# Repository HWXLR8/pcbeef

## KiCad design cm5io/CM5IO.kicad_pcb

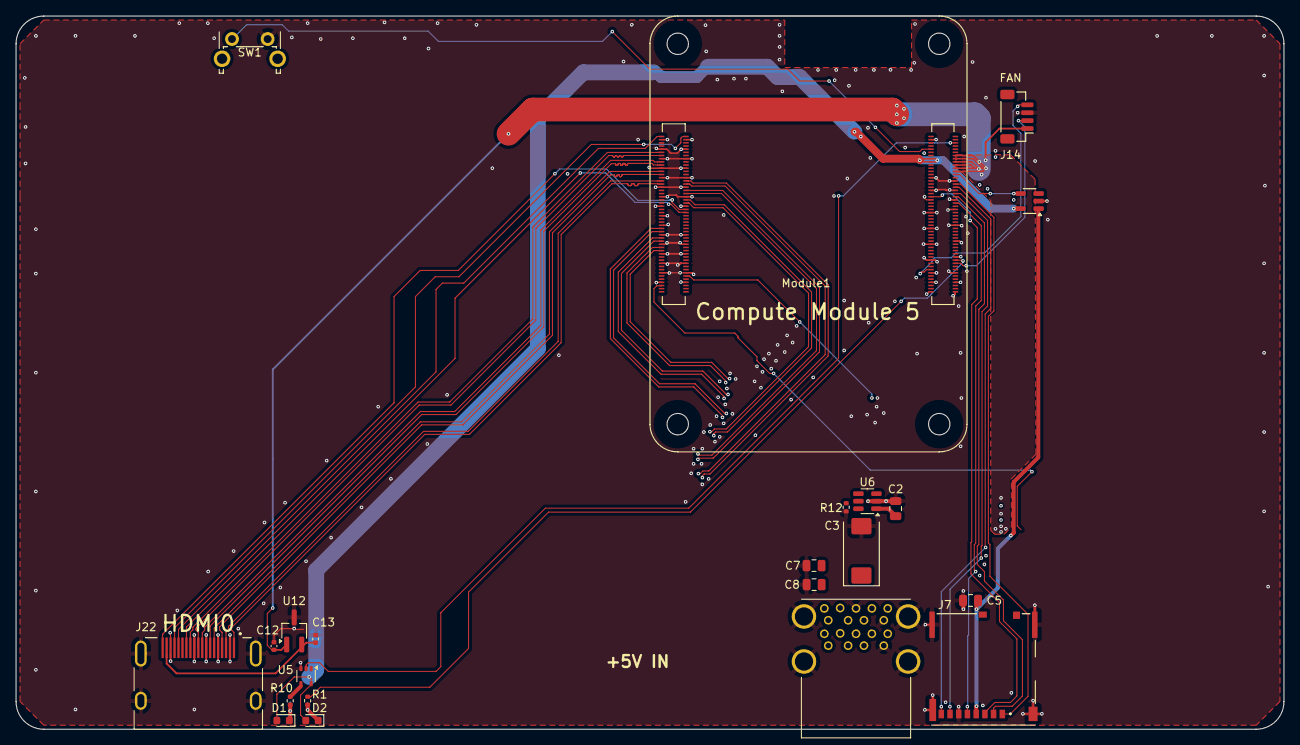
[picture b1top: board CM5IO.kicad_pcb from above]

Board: 4 copper layers, 160.0 x 90.0 mm, 22 parts (0 on the bottom side), 48 nets.

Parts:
C2, C5, C7, C8: 10u; C_0805_2012Metric
C3: 100uF; CP_EIA-7343-31_Kemet-D
C12, C13: 100n; C_0402_1005Metric
D1: LED Red; LED_0603_1608Metric
D2: LED Green; LED_0603_1608Metric
J7: Micro_SD_Card_Det; SDCARD_MOLEX_503398-1892
J12: USB3_A; MTCONN_UBAF30-D2011
J14: JST_SHBM04B-SRSS-TB; JST_SH_BM04B-SRSS-TB_1x04-1MP_P1.00mm_Vertical
J22: 690-019-298-412; EDAC 690-019-298-412
Module1: ComputeModule5-CM5; Raspberry-Pi-5-Compute-Module
R1, R10: 1k; R_0402_1005Metric
R12: 15K 1%; R_0402_1005Metric
SW1: Power button; SW_Tactile_SPST_Angled_PTS645Vx58-2LFS
U5: 74LVC1G07SE-7; SOT-353_SC-70-5
U6: AP22653W6; SOT-23-6
U12: RT9742SNGV; TSOT-23_HandSoldering
U18: RT9742GGJ5; SOT-23-5

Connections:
/+3.3v: D1.2 (A), D2.2 (A), Module1.84 (+3.3v_(Output)), Module1.86 (+3.3v_(Output)), U5.5 (VCC), U18.5 (IN)
/+5v: C2.1, C12.1, J14.1, Module1.77 (+5v_(Input)), Module1.79 (+5v_(Input)), Module1.81 (+5v_(Input)), Module1.83 (+5v_(Input)), Module1.85 (+5v_(Input)), Module1.87 (+5v_(Input)), U6.1 (IN), U12.1 (IN)
/CM5_GPIO ( Ethernet, GPIO, SDCARD)/+1.8v: Module1.88 (+1.8v_(Output)), Module1.90 (+1.8v_(Output))
/CM5_GPIO ( Ethernet, GPIO, SDCARD)/PWM: J14.2, Module1.19 (FAN_PWM)
/CM5_GPIO ( Ethernet, GPIO, SDCARD)/PWR_BUT: Module1.92 (PWR_BUT), SW1.1
/CM5_GPIO ( Ethernet, GPIO, SDCARD)/SD_CLK: J7.5 (CLK), Module1.57 (SD_CLK)
/CM5_GPIO ( Ethernet, GPIO, SDCARD)/SD_CMD: J7.3 (CMD), Module1.62 (SD_CMD)
/CM5_GPIO ( Ethernet, GPIO, SDCARD)/SD_DAT0: J7.7 (DAT0), Module1.63 (SD_DAT0)
/CM5_GPIO ( Ethernet, GPIO, SDCARD)/SD_DAT1: J7.8 (DAT1), Module1.67 (SD_DAT1)
/CM5_GPIO ( Ethernet, GPIO, SDCARD)/SD_DAT2: J7.1 (DAT2), Module1.69 (SD_DAT2)
/CM5_GPIO ( Ethernet, GPIO, SDCARD)/SD_DAT3: J7.2 (DAT3/CD), Module1.61 (SD_DAT3)
/CM5_GPIO ( Ethernet, GPIO, SDCARD)/SD_PWR: C5.1, J7.4 (VDD), U18.1 (OUT)
/CM5_GPIO ( Ethernet, GPIO, SDCARD)/SD_PWR_ON: Module1.75 (SD_PWR_ON), U18.4 (EN)
/CM5_GPIO ( Ethernet, GPIO, SDCARD)/TACHO: J14.4, Module1.16 (FAN_TACHO)
/CM5_GPIO ( Ethernet, GPIO, SDCARD)/nPWR_LED: Module1.95 (LED_nPWR), U5.2
/CM5_HighSpeed/HDMI0_CEC: J22.13 (CEC), Module1.151 (HDMI0_CEC)
/CM5_HighSpeed/HDMI0_CK_N: J22.12 (CK-), Module1.190 (HDMI0_CLK_N)
/CM5_HighSpeed/HDMI0_CK_P: J22.10 (CK+), Module1.188 (HDMI0_CLK_P)
/CM5_HighSpeed/HDMI0_D0_N: J22.9 (D0-), Module1.184 (HDMI0_TX0_N)
/CM5_HighSpeed/HDMI0_D0_P: J22.7 (D0+), Module1.182 (HDMI0_TX0_P)
/CM5_HighSpeed/HDMI0_D1_N: J22.6 (D1-), Module1.178 (HDMI0_TX1_N)
/CM5_HighSpeed/HDMI0_D1_P: J22.4 (D1+), Module1.176 (HDMI0_TX1_P)
/CM5_HighSpeed/HDMI0_D2_N: J22.3 (D2-), Module1.172 (HDMI0_TX2_N)
/CM5_HighSpeed/HDMI0_D2_P: J22.1 (D2+), Module1.170 (HDMI0_TX2_P)
/CM5_HighSpeed/HDMI0_HOTPLUG: J22.19 (HPD/HEAC-), Module1.153 (HDMI0_HOTPLUG)
/CM5_HighSpeed/HDMI0_SCL: J22.15 (SCL), Module1.200 (HDMI0_SCL)
/CM5_HighSpeed/HDMI0_SDA: J22.16 (SDA), Module1.199 (HDMI0_SDA)
/CM5_HighSpeed/HDMI_5v: C13.1, J22.18 (+5V), U12.2 (OUT)
/CM5_HighSpeed/USB3-0-D_N: J12.A2 (D-), Module1.136 (USB3-0-D_N)
/CM5_HighSpeed/USB3-0-D_P: J12.A3 (D+), Module1.134 (USB3-0-D_P)
/CM5_HighSpeed/USB3-0-RX_N: J12.A6 (SSRX+), Module1.128 (USB3-0-RX_N)
/CM5_HighSpeed/USB3-0-RX_P: J12.A5 (SSRX-), Module1.130 (USB3-0-RX_P)
/CM5_HighSpeed/USB3-0-TX_N: J12.A9 (SSTX+), Module1.140 (USB3-0-TX_N)
/CM5_HighSpeed/USB3-0-TX_P: J12.A8 (SSTX-), Module1.142 (USB3-0-TX_P)
/CM5_HighSpeed/USB3-1-D_N: J12.B2 (D-), Module1.165 (USB3-1-D_N)
/CM5_HighSpeed/USB3-1-D_P: J12.B3 (D+), Module1.163 (USB3-1-D_P)
/CM5_HighSpeed/USB3-1-RX_N: J12.B6 (SSRX+), Module1.157 (USB3-1-RX_N)
/CM5_HighSpeed/USB3-1-RX_P: J12.B5 (SSRX-), Module1.159 (USB3-1-RX_P)
/CM5_HighSpeed/USB3-1-TX_N: J12.B9 (SSTX+), Module1.169 (USB3-1-TX_N)
/CM5_HighSpeed/USB3-1-TX_P: J12.B8 (SSTX-), Module1.171 (USB3-1-TX_P)
/CM5_HighSpeed/VBUS: C3.1, C7.1, C8.1, J12.A1 (VBUS), J12.B1 (VBUS), U6.6 (OUT)
/CM5_HighSpeed/VBUS_EN: Module1.111 (VBUS_EN), U6.3 (EN)
GND: C2.2, C3.2, C5.2, C7.2, C8.2, C12.2, C13.2, J7.6 (VSS), J7.11 (SHIELD), J12.10 (SHIELD), J12.A4 (GND), J12.A7 (DRAIN), J12.B4 (GND), J12.B7 (DRAIN), J14.3, J22.2 (D2S), J22.5 (D1S), J22.8 (D0S), J22.11 (CKS), J22.17 (GND), J22.SH1 (SH), J22.SH2 (SH), J22.SH3 (SH), J22.SH4 (SH), Module1.1 (GND), Module1.2 (GND), Module1.7 (GND), Module1.8 (GND), Module1.13 (GND), Module1.14 (GND), Module1.22 (GND), Module1.23 (GND), Module1.32 (GND), Module1.33 (GND), Module1.42 (GND), Module1.43 (GND), Module1.52 (GND), Module1.53 (GND), Module1.59 (GND), Module1.60 (GND), Module1.65 (GND), Module1.66 (GND), Module1.71 (GND), Module1.74 (GND), Module1.98 (GND), Module1.107 (GND), Module1.108 (GND), Module1.113 (GND), Module1.114 (GND), Module1.119 (GND), Module1.120 (GND), Module1.125 (GND), Module1.126 (GND), Module1.131 (GND), Module1.132 (GND), Module1.137 (GND), Module1.138 (GND), Module1.144 (GND), Module1.150 (GND), Module1.155 (GND), Module1.156 (GND), Module1.161 (GND), Module1.162 (GND), Module1.167 (GND), Module1.168 (GND), Module1.173 (GND), Module1.174 (GND), Module1.179 (GND), Module1.180 (GND), Module1.185 (GND), Module1.186 (GND), Module1.191 (GND), Module1.192 (GND), Module1.197 (GND), Module1.198 (GND), R12.2, SW1.2, U5.3 (GND), U6.2 (GND), U12.3 (GND), U18.2 (GND)
unnamed: D1.1 (K), R10.1
unnamed: D2.1 (K), R1.1
unnamed: Module1.21 (LED_nACT), R1.2
unnamed: R10.2, U5.4
unnamed: R12.1, U6.5 (ILIM)

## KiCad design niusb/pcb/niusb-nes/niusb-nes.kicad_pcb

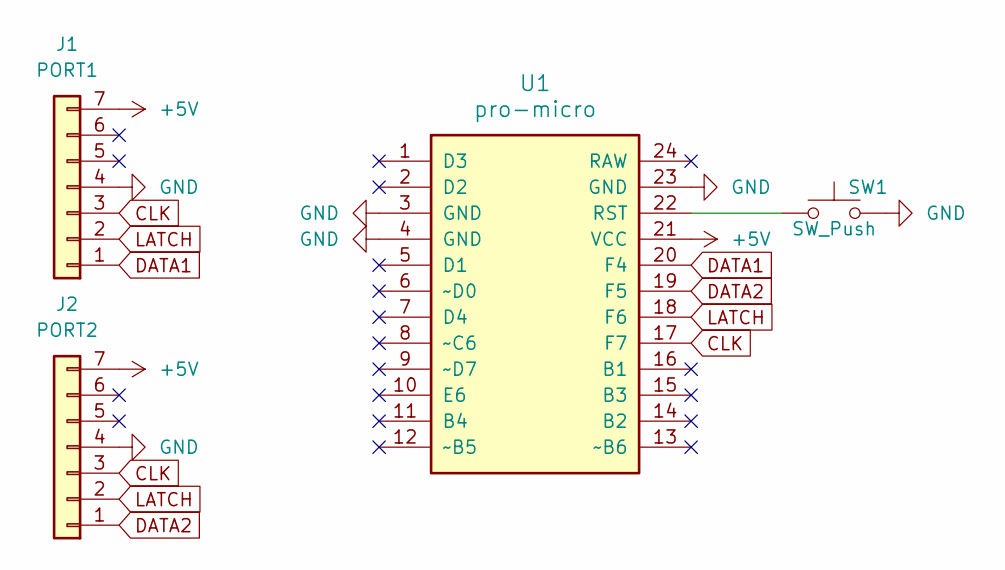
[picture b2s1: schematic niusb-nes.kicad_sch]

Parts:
J1: PORT1; nes-controller-port
J2: PORT2; nes-controller-port
SW1: SW_Push; SW_PUSH_6mm
U1: pro-micro

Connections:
+5V: J1.7, J2.7, U1.21 (VCC)
CLK: J1.3, J2.3, U1.17 (F7)
DATA1: J1.1, U1.20 (F4)
DATA2: J2.1, U1.19 (F5)
GND: J1.4, J2.4, SW1.2, U1.3 (GND), U1.4 (GND), U1.23 (GND)
LATCH: J1.2, J2.2, U1.18 (F6)
unnamed: SW1.1, U1.22 (RST)

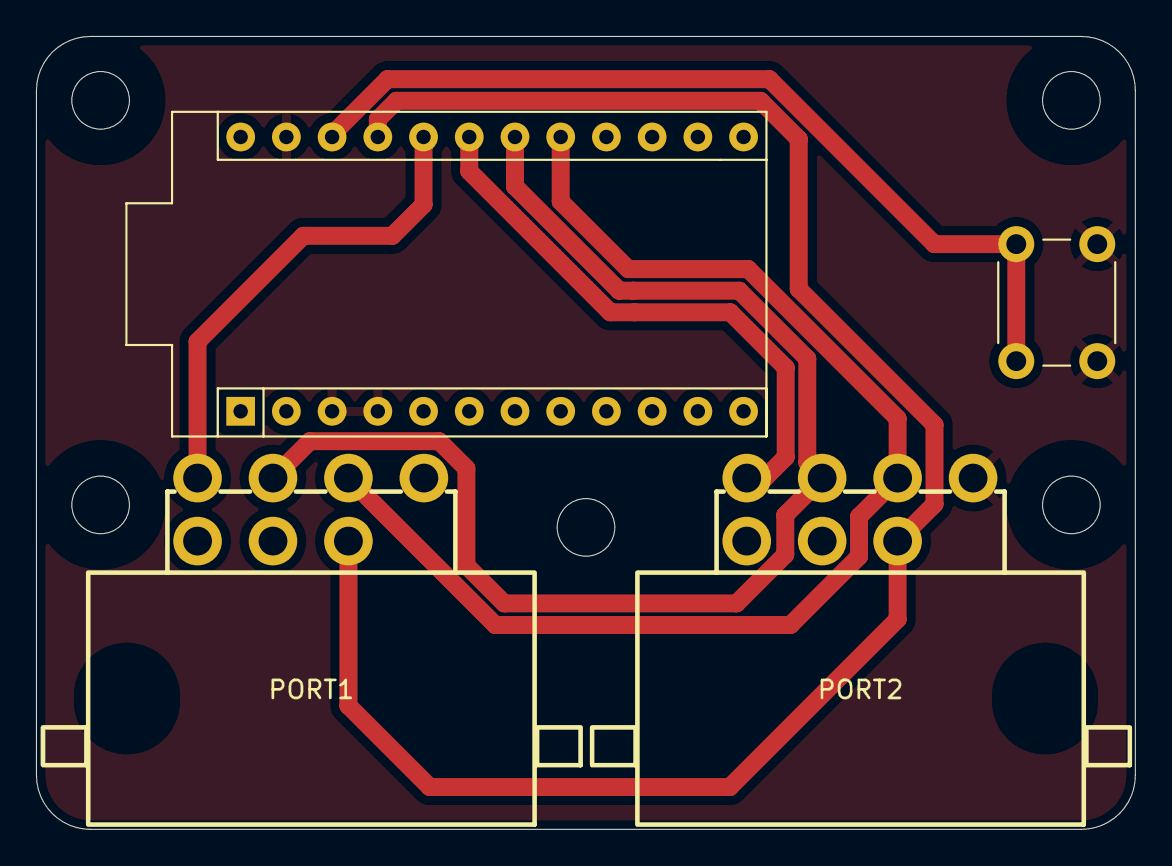
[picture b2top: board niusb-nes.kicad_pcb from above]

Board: 2 copper layers, 61.0 x 44.0 mm, 4 parts (0 on the bottom side), 7 nets.

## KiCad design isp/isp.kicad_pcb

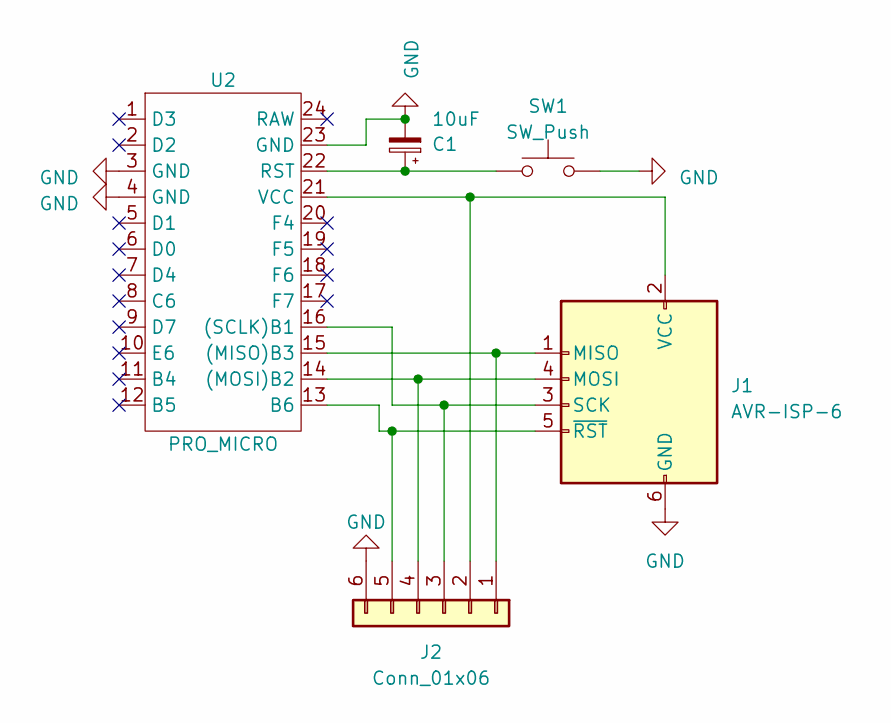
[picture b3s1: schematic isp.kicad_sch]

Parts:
C1: 10uF; CP_Radial_D5.0mm_P2.50mm
J1: AVR-ISP-6; IDC-Header_2x03_P2.54mm_Vertical
J2: Conn_01x06; PinHeader_1x06_P2.54mm_Vertical
SW1: SW_Push; SW_PUSH_6mm
U2: PRO_MICRO; ProMicro-NoSilk

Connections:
GND: C1.2, J1.6 (GND), J2.6, SW1.2, U2.3 (GND), U2.4 (GND), U2.23 (GND)
unnamed: J1.1 (MISO), J2.1, U2.15 ((MISO)B3)
unnamed: J1.4 (MOSI), J2.4, U2.14 ((MOSI)B2)
unnamed: J1.3 (SCK), J2.3, U2.16 ((SCLK)B1)
unnamed: J1.2 (VCC), J2.2, U2.21 (VCC)
unnamed: J1.5 (~RST), J2.5, U2.13 (B6)
unnamed: C1.1, SW1.1, U2.22 (RST)

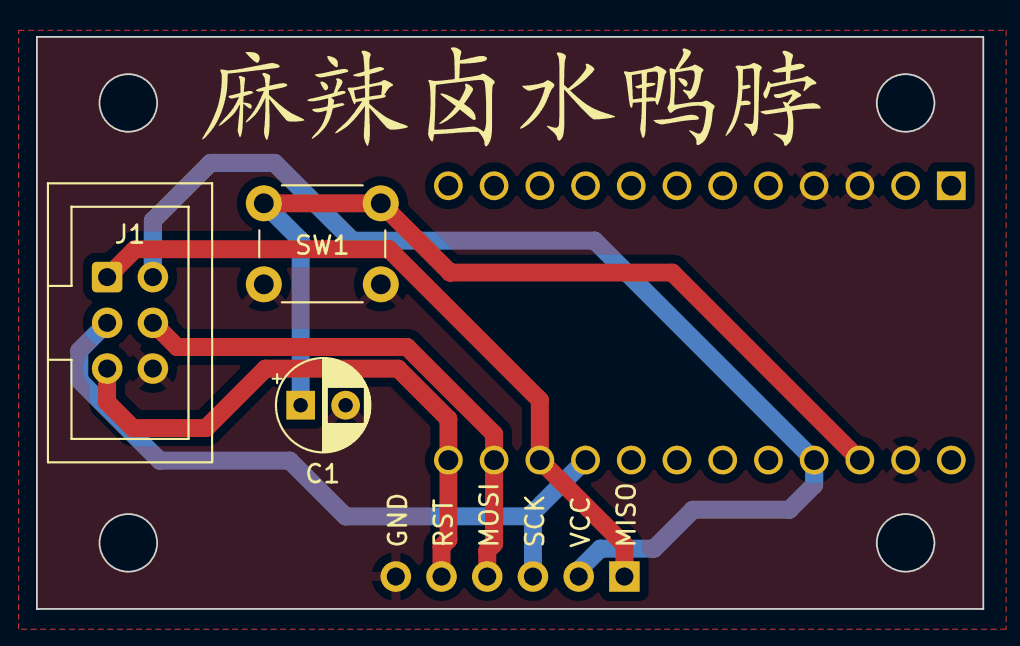
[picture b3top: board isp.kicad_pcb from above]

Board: 2 copper layers, 52.6 x 31.8 mm, 5 parts (0 on the bottom side), 7 nets.

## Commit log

2025-07-27 init
2025-07-27 [pibase] fix image path in readme
2025-07-27 add LICENSE
2025-08-01 [cm5io] remove USB-C and NVMe connectors, clean up routing
2025-08-01 ignore auto saved files
